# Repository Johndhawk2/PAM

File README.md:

# PAM
Personal At-home Monitoring device for diagnosis and treatment of patients

Here you'll find the code for the main board, as well as any CAD files or board schematics. For the code for the website, visit the johndhawk2.github.io repository.

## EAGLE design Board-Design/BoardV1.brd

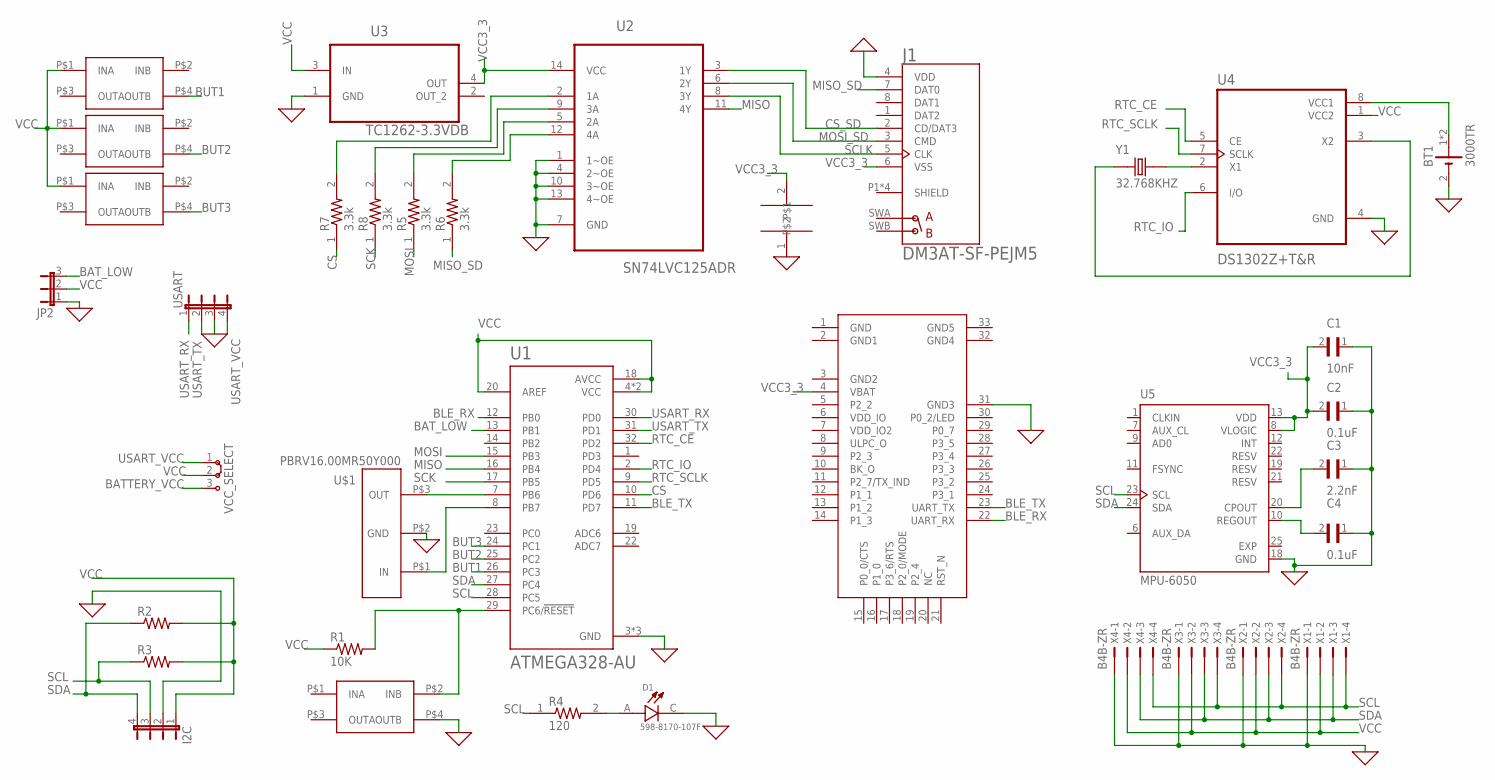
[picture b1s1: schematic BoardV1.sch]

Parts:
BT1: 3000TR; BAT_3000TR
C1: 10nF; CAPC2012X140N
C2, C4: 0.1uF; CAPC2012X140N
C3: 2.2nF; CAPC2012X140N
C5: CAPC3225X200N
D1: 598-8170-107F; LEDC2012X70N
I2C: JP4E; JP4
J1: DM3AT-SF-PEJM5; HRS_DM3AT-SF-PEJM5
JP2: JP2E; JP2
R1: 10K; RESC2012X65N
R2, R3: 7-1879534-9; RESC2012X65N
R4: 120; RESC2012X60
R5, R6, R7, R8: 3.3k; RESC2012X60
U1: ATMEGA328-AU; QFP80P900X900X120-32N
U2: SN74LVC125ADR; SOIC127P600X175-14N
U3: TC1262-3.3VDB; SOT230P700X180-4N
U4: DS1302Z+T&R; SOIC127P600X175-8N
U5: MPU-6050; QFN50P400X400X95-25N
U$1: PBRV16.00MR50Y000
U$2, U$3, U$4, U$5: SPST_SMD
U$6: RN4870; MICROCHIP_RN4677-V/RM100
USART: JP4E; JP4
VCC_SELECT: J2X2MM; 04C
X1, X2, X3, X4: B4B-ZR
Y1: 32.768KHZ; XTAL_ABS07-32.768KHZ-T

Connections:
0: BT1.2 (-), C1.1, C2.1, C3.1, C4.1, C5.1, D1.C, I2C.2, J1.4 (VDD), JP2.1, U1.3 (GND), U1.5 (GND), U1.21 (GND), U2.1 (1~OE), U2.4 (2~OE), U2.7 (GND), U2.10 (3~OE), U2.13 (4~OE), U3.1 (GND), U4.4 (GND), U5.18 (GND), U$1.P$2 (GND), U$2.P$4 (OUTB), U$6.31 (GND3), USART.3, X1.1, X2.1, X3.1, X4.1
BATTERY_VCC: VCC_SELECT.3
BAT_LOW: JP2.3, U1.13 (PB1)
BLE_RX: U1.12 (PB0), U$6.22 (UART_RX)
BLE_TX: U1.11 (PD7), U$6.23 (UART_TX)
BUT1: U1.26 (PC3), U$3.P$4 (OUTB)
BUT2: U1.25 (PC2), U$4.P$4 (OUTB)
BUT3: U1.24 (PC1), U$5.P$4 (OUTB)
CS: R7.1, U1.10 (PD6)
CS_SD: J1.2 (CD/DAT3), U2.3 (1Y)
EXP: U5.25 (EXP)
MISO: U1.16 (PB4), U2.11 (4Y)
MISO_SD: J1.7 (DAT0), R6.1
MOSI: R5.1, U1.15 (PB3)
MOSI_SD: J1.3 (CMD), U2.6 (2Y)
unnamed: R1.2, U1.29 (PC6/!RESET), U$2.P$2 (INB)
unnamed: U4.2 (X1), Y1.2
unnamed: U1.8 (PB7), U$1.P$1 (IN)
unnamed: U1.7 (PB6), U$1.P$3 (OUT)
unnamed: U4.3 (X2), Y1.1
unnamed: BT1.1 (+), BT1.3 (+), U4.8 (VCC1)
unnamed: C4.2, U5.10 (REGOUT)
unnamed: C3.2, U5.20 (CPOUT)
unnamed: R7.2, U2.2 (1A)
unnamed: D1.A, R4.2
unnamed: R8.2, U2.9 (3A)
unnamed: R5.2, U2.5 (2A)
unnamed: R6.2, U2.12 (4A)
RTC_CE: U1.32 (PD2), U4.5 (CE)
RTC_IO: U1.2 (PD4), U4.6 (I/O)
RTC_SCLK: U1.9 (PD5), U4.7 (SCLK)
SCK: R8.1, U1.17 (PB5)
SCL: I2C.3, R3.1, R4.1, U1.28 (PC5), U5.23 (SCL), X1.4, X2.4, X3.4, X4.4
SCLK: J1.5 (CLK), U2.8 (3Y)
SDA: I2C.4, R2.1, U1.27 (PC4), U5.24 (SDA), X1.3, X2.3, X3.3, X4.3
USART_RX: U1.30 (PD0), USART.1
USART_TX: U1.31 (PD1), USART.2
USART_VCC: USART.4, VCC_SELECT.1
VCC: I2C.1, JP2.2, R1.1, R2.2, R3.2, U1.4 (VCC), U1.6 (VCC), U1.18 (AVCC), U1.20 (AREF), U3.3 (IN), U4.1 (VCC2), U$3.P$1 (INA), U$4.P$1 (INA), U$5.P$1 (INA), VCC_SELECT.2, X1.2, X2.2, X3.2, X4.2
VCC3_3: C1.2, C2.2, C5.2, J1.6 (VSS), U2.14 (VCC), U3.4 (OUT), U5.8 (VLOGIC), U5.13 (VDD), U$6.4 (VBAT)

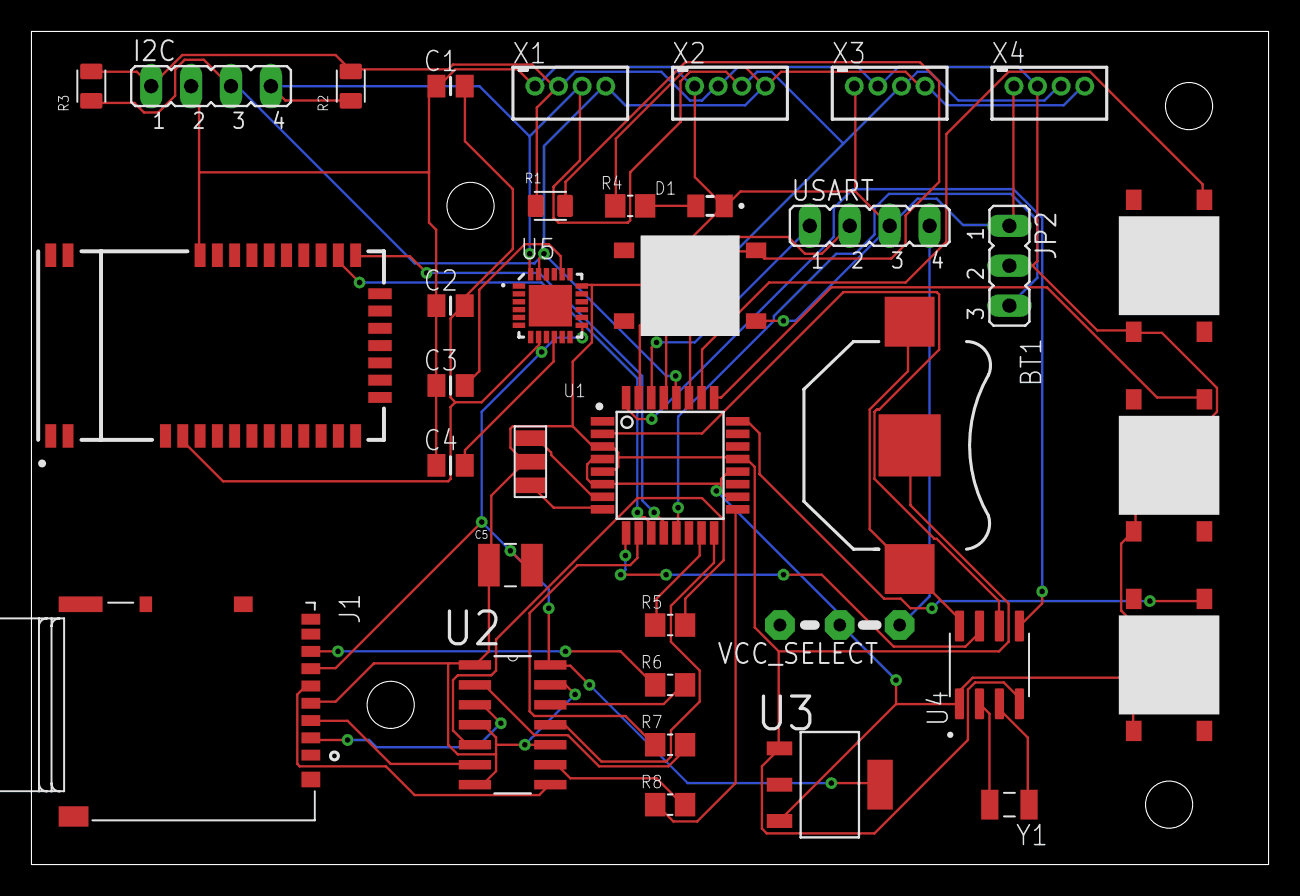
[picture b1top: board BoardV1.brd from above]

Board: 2 copper layers, 78.7 x 53.0 mm, 36 parts (0 on the bottom side), 38 nets.
